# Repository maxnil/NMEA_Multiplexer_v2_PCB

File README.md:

# NMEA_Multiplexer_v2_PCB
NMEA Multiplexer v2 PCB

Updated version of the old 2010 NMEA Miltiplexer.
This new improved version has support for 5 NMEA interfaces, USB as well as a BlueTooth module.

Firmware for this board is can be found in the https://github.com/maxnil/NMEA_Multiplexer_v2.0_FW repository.

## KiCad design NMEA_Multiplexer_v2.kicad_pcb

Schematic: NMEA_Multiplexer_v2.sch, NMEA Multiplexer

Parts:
C1, C2, C3, C4, C5, C6, C9, C10, C12, C13, C15, C16, C17, C18, C19, C20, C21, C22, C24, C26, C27, C28, C29: 100n; C_0603
C7, C8: 5n; C_0603
C11, C23: 4.7u; C_0603
C14: 10u; CP_Elec_4x5.8
C25: 2.2u; C_0603
D1: Tx 3 (green); LED_0603
D2: Err 3 (red); LED_0603
D3: Rx 3 (green); LED_0603
D4: Tx 4 (green); LED_0603
D5: Err 4 (red); LED_0603
D6: Rx 4 (green); LED_0603
D7: PWR (green); LED_0603
D8: BT Con (blue); LED_0603
D9: Tx BT (green); LED_0603
D10: Rx BT (green); LED_0603
D11: Tx (green); LED_0603
D12: Err 2 (red); LED_0603
D13: Rx 2 (green); LED_0603
D14: Tx 1 (green); LED_0603
D15: Err 1 (red); LED_0603
D16: Rx 1 (green); LED_0603
D17: Tx 0 (green); LED_0603
D18: Err 0 (red); LED_0603
D19: Rx 0 (green); LED_0603
J1: USB; USB_Mini-B
J2: Port 1; TerminalBlock_Pheonix_PT-3.5mm_3pol
J3: Port 2; TerminalBlock_Pheonix_PT-3.5mm_3pol
J4: Port 3; TerminalBlock_Pheonix_PT-3.5mm_3pol
J5: Port 4; TerminalBlock_Pheonix_PT-3.5mm_3pol
J6: Port 5; TerminalBlock_Pheonix_PT-3.5mm_3pol
J7: 12V; TerminalBlock_Pheonix_PT-3.5mm_2pol
J8: DEBUG UART; Pin_Header_Straight_1x03_Pitch2.54mm
J9: JTAG; Pin_Header_Straight_2x05_Pitch1.27mm_SMD
JP1: ERASE; Pin_Header_Straight_1x02_Pitch2.00mm
R1, R2, R3, R4, R5, R6, R7, R8, R9, R13, R18, R19, R20, R21, R22, R23, R27, R28, R29: 220; R_0603
R10, R12, R16, R17: 39; R_0603
R11, R24, R25, R26: 100k; R_0603
R14: 27k; R_0603
R15: 47k; R_0603
SW1: Reset; SW_SPST_EVQP2
U1: ATSAMG55J19A-AU; LQFP-64_10x10mm_Pitch0.5mm
U2, U3: XR32330; QFN-24_4x4mm_Pitch0.5mm_NoMask
U4: LF33ABDT-TR; TO-252-2_Rectifier
U5: HM-11
Y1: 32.768k; Crystal_SMD_3215-2pin_3.2x1.5mm

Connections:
+1V8: C9.1, C25.1, C26.1, C29.1, U1.9, U1.30, U1.45
+3V3: C1.1, C2.1, C10.1, C11.1, C12.1, C14.1, C16.1, C17.1, C22.1, C23.1, C24.1, C27.1, C28.1, J9.1, JP1.1, R9.1, R11.1, R24.1, R25.1, R26.1, U1.1, U1.26, U1.27, U1.28, U1.31, U1.32, U1.64, U2.14, U2.15, U2.18, U2.19, U3.14, U3.15, U3.18, U3.19, U4.3, U5.9 (VCC)
/BT_KEY: U1.23, U5.16 (KEY/PIO0)
/BT_RESET_N: U1.51, U5.11 (~RESET)
/CTS0: U1.56, U5.1 (UART_RTS)
/DM: R17.1, U1.25
/DP: R16.1, U1.24
/LED_0_ERR: R29.1, U1.58
/LED_0_RX: R27.1, U1.57
/LED_0_TX: R28.1, U1.59
/LED_1_ERR: R22.1, U1.41
/LED_1_RX: R21.1, U1.36
/LED_1_TX: R23.1, U1.44
/LED_2_ERR: R19.1, U1.34
/LED_2_RX: R20.1, U1.35
/LED_2_TX: R18.1, U1.33
/LED_3_ERR: R2.1, U1.19
/LED_3_RX: R1.1, U1.20
/LED_3_TX: R3.1, U1.18
/LED_4_ERR: R6.1, U1.15
/LED_4_RX: R5.1, U1.14
/LED_4_TX: R4.1, U1.16
/LED_BT_CON: R13.1, U5.15 (LED/PIO1)
/LED_BT_RX: R7.1, U1.61
/LED_BT_TX: R8.1, U1.60
/RTS0: U1.52, U5.3 (UART_CTS)
/RX0: J2.3, U3.3
/RX1: J3.3, U3.2
/RX2: J4.3, U3.1
/RX3: J5.3, U2.2
/RX4: J6.3, U2.1
/RXD0: U1.49, U5.2 (UART_TX)
/RXD1: U1.39, U3.11
/RXD2: U1.8, U2.12
/RXD3: U1.4, U2.11
/RXD4: J8.3, U1.47
/RXD5: U1.43, U3.10
/RXD6: U1.38, U3.12
/TCK: J9.4, R25.2, U1.55
/TDI: J9.8, R26.2, U1.62
/TDO: J9.6, U1.50
/TMS: J9.2, R24.2, U1.54
/TX0: J2.1, U3.6
/TX1: J3.1, U3.5
/TX2: J4.1, U3.4
/TX3: J5.1, U2.4
/TX4: J6.1, U2.5
/TXD0: U1.48, U5.4 (UART_RX)
/TXD1: U1.40, U3.8
/TXD2: U1.17, U2.8
/TXD3: U1.5, U2.9
/TXD4: J8.2, U1.46
/TXD5: U1.42, U3.7
/TXD6: U1.37, U3.9
/VBUS_3.3V: R14.2, R15.1, U1.22
/XIN32: C8.1, U1.11, Y1.1
/XOUT32: C7.1, U1.12, Y1.2
/nRST: J9.10, R10.1, U1.2
GND: C1.2, C2.2, C3.1, C5.1, C7.2, C8.2, C9.2, C10.2, C11.2, C12.2, C13.2, C14.2, C15.2, C16.2, C17.2, C18.1, C20.1, C22.2, C23.2, C24.2, C25.2, C26.2, C27.2, C28.2, C29.2, D1.1, D2.1, D3.1, D4.1, D5.1, D6.1, D7.1, D8.1, D9.1, D10.1, D11.1, D12.1, D13.1, D14.1, D15.1, D16.1, D17.1, D18.1, D19.1, J1.5, J1.6, J2.2, J3.2, J4.2, J5.2, J6.2, J7.2, J8.1, J9.3, J9.5, R15.2, SW1.1, U1.13, U1.29, U1.53, U2.3, U2.7, U2.17, U2.25, U3.17, U3.25, U4.2, U5.12 (GND)
unnamed: C3.2, U2.20
unnamed: C4.1, U2.22
unnamed: C4.2, U2.23
unnamed: C5.2, U2.24
unnamed: C6.1, U2.21
unnamed: C6.2, U2.16
unnamed: C13.1, R10.2, R11.2, R12.1
unnamed: C15.1, J7.1, U4.1
unnamed: C18.2, U3.20
unnamed: C19.1, U3.22
unnamed: C19.2, U3.23
unnamed: C20.2, U3.24
unnamed: C21.1, U3.21
unnamed: C21.2, U3.16
unnamed: D1.2, R3.2
unnamed: D2.2, R2.2
unnamed: D3.2, R1.2
unnamed: D4.2, R4.2
unnamed: D5.2, R6.2
unnamed: D6.2, R5.2
unnamed: D7.2, R9.2
unnamed: D8.2, R13.2
unnamed: D9.2, R8.2
unnamed: D10.2, R7.2
unnamed: D11.2, R18.2
unnamed: D12.2, R19.2
unnamed: D13.2, R20.2
unnamed: D14.2, R23.2
unnamed: D15.2, R22.2
unnamed: D16.2, R21.2
unnamed: D17.2, R28.2
unnamed: D18.2, R29.2
unnamed: D19.2, R27.2
unnamed: J1.1, R14.1
unnamed: J1.2, R17.2
unnamed: J1.3, R16.2
unnamed: JP1.2, U1.3
unnamed: R12.2, SW1.2

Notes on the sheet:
Close to VDDIO
Close to VDDCORE
Close to VDDOUT
Close to VDDUSB

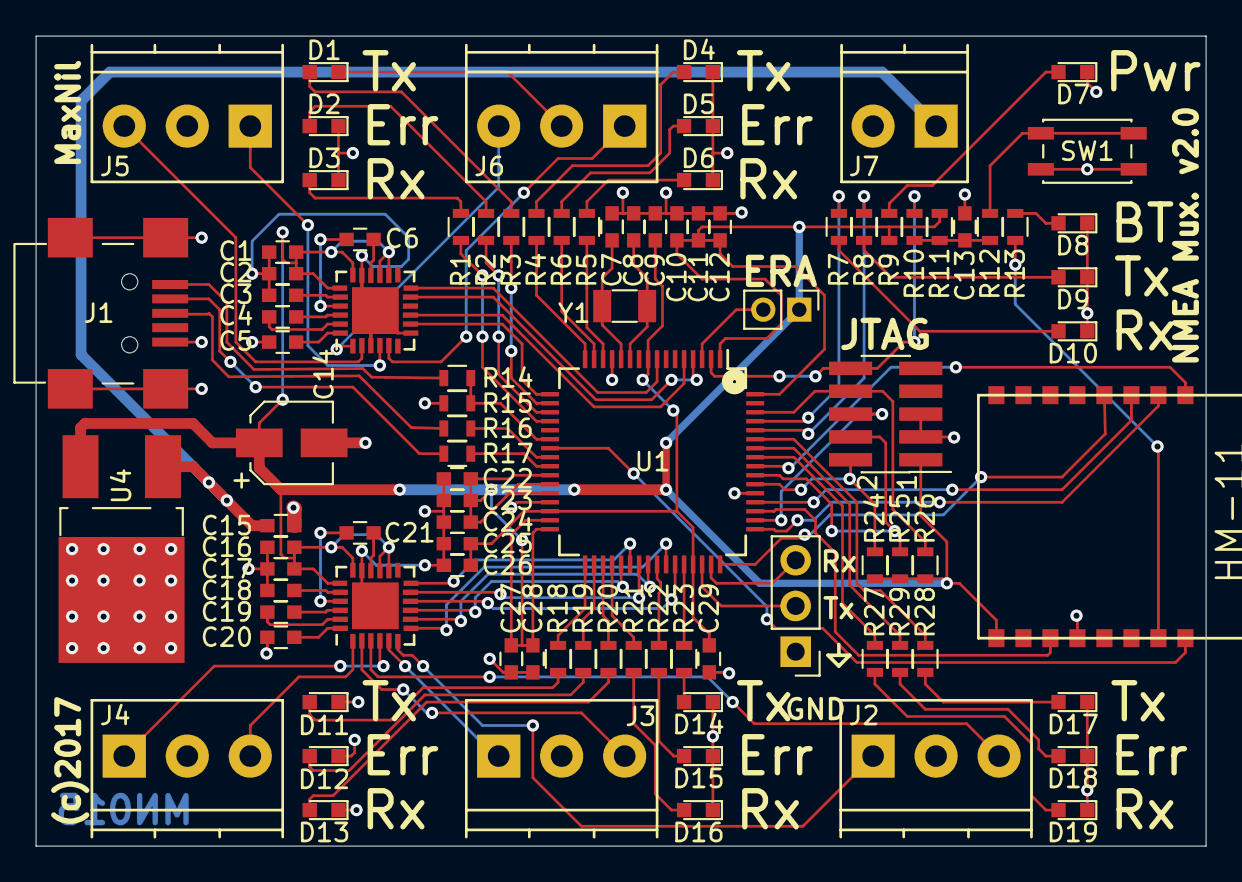
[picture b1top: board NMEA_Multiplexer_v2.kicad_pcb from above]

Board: 2 copper layers, 65.0 x 45.0 mm, 94 parts (0 on the bottom side), 97 nets.

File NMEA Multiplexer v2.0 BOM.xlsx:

Reference | Value | Footprint | DigiKey part number
SW1 | Reset | Buttons_Switches_SMD:SW_SPST_EVQP2 | P12297SCT-ND
C1 | 0.1u | Capacitors_SMD:C_0603 | 1276-1006-1-ND
C2 | 0.1u | Capacitors_SMD:C_0603 | 1276-1006-1-ND
C3 | 0.1u | Capacitors_SMD:C_0603 | 1276-1006-1-ND
C4 | 0.1u | Capacitors_SMD:C_0603 | 1276-1006-1-ND
C5 | 0.1u | Capacitors_SMD:C_0603 | 1276-1006-1-ND
C6 | 0.1u | Capacitors_SMD:C_0603 | 1276-1006-1-ND
C9 | 0.1u | Capacitors_SMD:C_0603 | 1276-1006-1-ND
C10 | 0.1u | Capacitors_SMD:C_0603 | 1276-1006-1-ND
C12 | 0.1u | Capacitors_SMD:C_0603 | 1276-1006-1-ND
C13 | 0.1u | Capacitors_SMD:C_0603 | 1276-1006-1-ND
C15 | 0.1u | Capacitors_SMD:C_0603 | 1276-1006-1-ND
C16 | 0.1u | Capacitors_SMD:C_0603 | 1276-1006-1-ND
C17 | 0.1u | Capacitors_SMD:C_0603 | 1276-1006-1-ND
C18 | 0.1u | Capacitors_SMD:C_0603 | 1276-1006-1-ND
C19 | 0.1u | Capacitors_SMD:C_0603 | 1276-1006-1-ND
C20 | 0.1u | Capacitors_SMD:C_0603 | 1276-1006-1-ND
C21 | 0.1u | Capacitors_SMD:C_0603 | 1276-1006-1-ND
C22 | 0.1u | Capacitors_SMD:C_0603 | 1276-1006-1-ND
C24 | 0.1u | Capacitors_SMD:C_0603 | 1276-1006-1-ND
C26 | 0.1u | Capacitors_SMD:C_0603 | 1276-1006-1-ND
C27 | 0.1u | Capacitors_SMD:C_0603 | 1276-1006-1-ND
C28 | 0.1u | Capacitors_SMD:C_0603 | 1276-1006-1-ND
C29 | 0.1u | Capacitors_SMD:C_0603 | 1276-1006-1-ND
C25 | 2.2u | Capacitors_SMD:C_0603 | 399-7886-1-ND
C11 | 4.7u | Capacitors_SMD:C_0603 | 1276-1784-1-ND
C23 | 4.7u | Capacitors_SMD:C_0603 | 1276-1784-1-ND
C7 | 5p | Capacitors_SMD:C_0603 | 1276-2129-1-ND
C8 | 5p | Capacitors_SMD:C_0603 | 1276-2129-1-ND
C14 | 10u | Capacitors_SMD:CP_Elec_4x5.8 | 399-6695-1-ND
J7 | 12V | Connectors_Terminal_Blocks:TerminalBlock_Pheonix_PT-3.5mm_2pol | ED2740-ND
J2 | Port 1 | Connectors_Terminal_Blocks:TerminalBlock_Pheonix_PT-3.5mm_3pol | ED2741-ND
J3 | Port 2 | Connectors_Terminal_Blocks:TerminalBlock_Pheonix_PT-3.5mm_3pol | ED2741-ND
J4 | Port 3 | Connectors_Terminal_Blocks:TerminalBlock_Pheonix_PT-3.5mm_3pol | ED2741-ND
J5 | Port 4 | Connectors_Terminal_Blocks:TerminalBlock_Pheonix_PT-3.5mm_3pol | ED2741-ND
J6 | Port 5 | Connectors_Terminal_Blocks:TerminalBlock_Pheonix_PT-3.5mm_3pol | ED2741-ND
J1 | USB | Connectors:USB_Mini-B | H2959CT-ND
Y1 | 32.768k | Crystals:Crystal_SMD_3215-2pin_3.2x1.5mm | 631-1002-1-ND
U2 | XR32330 | Housings_DFN_QFN:QFN-24_4x4mm_Pitch0.5mm_NoMask | 1016-2177-ND
U3 | XR32330 | Housings_DFN_QFN:QFN-24_4x4mm_Pitch0.5mm_NoMask | 1016-2177-ND
U1 | ATSAMG55J19A-AU | Housings_QFP:LQFP-64_10x10mm_Pitch0.5mm | 1611-ATSAMG55J19A-AUTCT-ND
D8 | BT Con (blue) | LEDs:LED_0603 | 475-2815-1-ND
D18 | Err 0 (red) | LEDs:LED_0603 | 511-1586-1-ND
D15 | Err 1 (red) | LEDs:LED_0603 | 511-1586-1-ND
D12 | Err 2 (red) | LEDs:LED_0603 | 511-1586-1-ND
D2 | Err 3 (red) | LEDs:LED_0603 | 511-1586-1-ND
D5 | Err 4 (red) | LEDs:LED_0603 | 511-1586-1-ND
D7 | PWR (white) | LEDs:LED_0603 | 511-1602-1-ND
D19 | Rx 0 (green) | LEDs:LED_0603 | 511-1584-1-ND
D16 | Rx 1 (green) | LEDs:LED_0603 | 511-1584-1-ND
D13 | Rx 2 (green) | LEDs:LED_0603 | 511-1584-1-ND
D3 | Rx 3 (green) | LEDs:LED_0603 | 511-1584-1-ND
D6 | Rx 4 (green) | LEDs:LED_0603 | 511-1584-1-ND
D10 | Rx BT (green) | LEDs:LED_0603 | 511-1584-1-ND
D11 | Tx (green) | LEDs:LED_0603 | 511-1584-1-ND
D17 | Tx 0 (green) | LEDs:LED_0603 | 511-1584-1-ND
D14 | Tx 1 (green) | LEDs:LED_0603 | 511-1584-1-ND
D1 | Tx 3 (green) | LEDs:LED_0603 | 511-1584-1-ND
D4 | Tx 4 (green) | LEDs:LED_0603 | 511-1584-1-ND
D9 | Tx BT (green) | LEDs:LED_0603 | 511-1584-1-ND
U5 | HM-11 | MaxNil:HM-11 | n/a
JP1 | ERASE | Pin_Headers:Pin_Header_Straight_1x02_Pitch2.00mm | 952-2326-ND
J8 | DEBUG UART | Pin_Headers:Pin_Header_Straight_1x03_Pitch2.54mm | S1011EC-40-ND
J9 | JTAG | Pin_Headers:Pin_Header_Straight_2x05_Pitch1.27mm_SMD | 609-3741-ND
R10 | 39 | Resistors_SMD:R_0603 | 311-39.0HRCT-ND
R12 | 39 | Resistors_SMD:R_0603 | 311-39.0HRCT-ND
R16 | 39 | Resistors_SMD:R_0603 | 311-39.0HRCT-ND
R17 | 39 | Resistors_SMD:R_0603 | 311-39.0HRCT-ND
R13 | 120 | Resistors_SMD:R_0603
R1 | 220 | Resistors_SMD:R_0603 | 311-220HRCT-ND
R2 | 220 | Resistors_SMD:R_0603 | 311-220HRCT-ND
R3 | 220 | Resistors_SMD:R_0603 | 311-220HRCT-ND
R4 | 220 | Resistors_SMD:R_0603 | 311-220HRCT-ND
R5 | 220 | Resistors_SMD:R_0603 | 311-220HRCT-ND
R6 | 220 | Resistors_SMD:R_0603 | 311-220HRCT-ND
R7 | 220 | Resistors_SMD:R_0603 | 311-220HRCT-ND
R8 | 220 | Resistors_SMD:R_0603 | 311-220HRCT-ND
R18 | 220 | Resistors_SMD:R_0603 | 311-220HRCT-ND
R19 | 220 | Resistors_SMD:R_0603 | 311-220HRCT-ND
R20 | 220 | Resistors_SMD:R_0603 | 311-220HRCT-ND
R21 | 220 | Resistors_SMD:R_0603 | 311-220HRCT-ND
R22 | 220 | Resistors_SMD:R_0603 | 311-220HRCT-ND
R23 | 220 | Resistors_SMD:R_0603 | 311-220HRCT-ND
R27 | 220 | Resistors_SMD:R_0603 | 311-220HRCT-ND
R28 | 220 | Resistors_SMD:R_0603 | 311-220HRCT-ND
R29 | 220 | Resistors_SMD:R_0603 | 311-220HRCT-ND
R9 | 82 | Resistors_SMD:R_0603 | 311-82.0HRCT-ND
R11 | 100k | Resistors_SMD:R_0603 | 311-100KHRCT-ND
R24 | 100k | Resistors_SMD:R_0603 | 311-100KHRCT-ND
R25 | 100k | Resistors_SMD:R_0603 | 311-100KHRCT-ND
R26 | 100k | Resistors_SMD:R_0603 | 311-100KHRCT-ND
R14 | 27k | Resistors_SMD:R_0603 | 311-27.0KHRCT-ND
R15 | 47k | Resistors_SMD:R_0603 | 311-47.0KHRCT-ND
U4 | LF33ABDT-TR | TO_SOT_Packages_SMD:TO-252-2_Rectifier | 497-5225-1-ND

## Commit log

2017-04-17 First version
2017-04-17 Added ignore of cache file
2017-05-04 First complete schematic
2017-05-04 Fixed some pin-errors in the ATSAM symbol Swapped place between LED and resistor
2017-05-09 Schematic ok Most of components placed on PCB
2017-05-14 Before the renaming
2017-05-20 Fixed missing decaps on VDDCORE
2017-05-20 Placement complete
2017-05-25 Swapped LED_BT_TX with LED_BT_RX
2017-05-25 Bottom half completed
2017-05-25 Removed from repository
2017-05-25 Corrected description
2017-06-08 Swapped values between C11 and C12
2017-06-08 More connections
2017-07-08 Soon complete
2017-07-11 Everything connected!
2017-07-12 Added copyright and board text
2017-07-12 First version of the Gerber files
2017-07-15 Updated USB footprint Connected BT KEY pin
